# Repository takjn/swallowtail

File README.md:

# Swallowtail
A split keyboard with 5x6 column staggered keys.

## Parts List
### Required

|Name |Number |Notes |
|--- |--- |--- |
|PCB | 2 | This PCB is reversible. One is for left and the other is for right. You can use a gerber file in `pcb/plot` directory to order your one. |
|Top plate, bottom plate, OLED protection plate | 2 sets | You can see the svg file in `plate` directory. This is designed for 2mm acrylic plate. If you create your plate with another thickness or material, you may need to change spacer height and screw length. |
|3mm female-to-female spacer | 12 |https://www.aliexpress.com/item/33033691154.html |
|3mm female-to-male spacer | 16 |https://www.aliexpress.com/item/33033691154.html |
|8mm female-to-female spacer | 4 |https://www.aliexpress.com/item/33033691154.html |
|M2 3mm screw | 32 | 3.5mm will be better if you can get. |
|Diode 1N4148 | 60 | |
|Kailh PCB Socket | 60 | |
|2 pin Tactile switch | 2 | For reset switch |
|3.5mm TRRS jack | 2 | |
|Adhesive Rubber Cushions | 8 | |
|Pro micro | 2 | |
|Cherry MX switch (5 pin) | 60 | |
|Keycaps | 60 | 58 1u keycaps and 2 1.5u (or up to 2.25u) keycaps|
|TRS (3 pole) audio cable | 1 | |
|Micro USB Cable | 1 | |

### Options
#### Spring loaded pin headers
Highly recommend for beginners. Some shop sell it with a Pro micro.
|Name |Number |Notes |
|--- |--- |--- |
|Spring loaded 12-pin header (a.k.a. Conthrough) | 4 |https://talpkeyboard.net/items/5e056626d790db16e2889233  |

#### OLED
Just a decorative parts.
|Name |Number |Notes |
|--- |--- |--- |
|SSD1306 OLED module | 2 | |
|4 pin low profile socket (low profile)| 2 | |
|4 pin low profile header (low profile)| 2 | |

#### Back light
A led places in bottom (south) side of keycap. Transparent key switch is recommended.
|Name |Number |Notes |
|--- |--- |--- |
|SK6812MINI-E | 60 | |

## Build Instructions

### Preparation
#### QMK firmware
Swallowtail uses QMK firmware. See firmware section and flush a firmware to Pro micro in advance.

#### Pro micro
Pro micro USB connector is fragile. You can reinforce the connector with epoxy resin adhesive. Put a small amount of epoxy resin around the connector. Be careful not to flow it into the connector. Leave it until fixed.

### Soldering
All parts have a position and orientation. See the photo to make sure it is placed correctly before soldering.

Maybe a good idea to use masking tape to hold parts before soldering.

#### Bridge jumpers
The PCB is reversible. Use one board for the left and the other for the right.
Bridge five jumpers on each board. One should be "Left" and the other should be "Right".

#### Diode
Place diodes on the back side of the pcb. This is the same side on which you jumpered. Make sure the diode orientation is correct. All diodes orientation must be the same on a pcb.

#### Reset switch and TRRS jack
Solder a reset switch and TRRS jack on the **front** side of the pcb.

#### Pro micro
Insert pin headers from the surface on which parts are mounted. Solder it from the **blank** side of the Pro micro.

Insert a Pro micro into the place on the PCB. If you are using spring loaded pin headers, you don't need to solder it on the PCB so that you can remove Pro micro later easily. If you don't, solder it and cut pins a little not to conflict with the cover plate.

#### Test
Before moving to the next step, test the pcb once. Flash a firmware to the Pro micro. Then, make short-circuit on each keyswitch pads. You will see some characters in your computer.

#### Kailh PCB Socket
Place a PCB socket on the back side of pcb. Make sure the position is correct.

#### OLED (optional)
Place a pin socket on the **front** side and solder it. Then solder a pin header on a OLED.

#### Back light (optional)
See a LED. You will see one of pins' corner is cut. The pin should be placed on the bottom-left in where a "L" shape silk is printed.

LED can be broken easily by heat. Be careful not to take too long time to solder. I usually solder only one pin at once and go to the next LED. After all LEDs in a row is fixed, back to the first LED to solder the second pin and repeat the process. This will be good not to heat too much on a LED.

### Assemble
Screw top plate spacers. 3mm female-to-male spacer should be on the front side. Attach a PCB and fix the PCB with a 3mm female-to-female spacer from the back side.

Screw OLED spacers. Each 8mm female-to-female spacer should be on the front side. Fix the spacer with a 3mm female-to-male spacer from the back side.

Put the bottom plate and OLED protection plate too.

Plug key switches on the top plate. Make sure all pins are straight before insert.

## Firmware
You can use a prebuilt firmware in the firmware directory. Go to [Pro Micro Web Updater](https://sekigon-gonnoc.github.io/promicro-web-updater/index.html) and flash the hex file in the firmware directory.

The firmware supports [Remap](https://remap-keys.app/). You can customize key bindings easily without compile. Go to [Remap](https://remap-keys.app/) and connect your keyboad.

Swallowtail uses QMK firmware. If you want to customize the firmware, see [swallowtail branch in takjn/qmk_firmware](https://github.com/takjn/qmk_firmware/tree/swallowtail/keyboards/swallowtail).

## License
Licensed under the MIT License.

## Dependencies
This PCB uses [foostan/kbd](https://github.com/foostan/kbd) library.

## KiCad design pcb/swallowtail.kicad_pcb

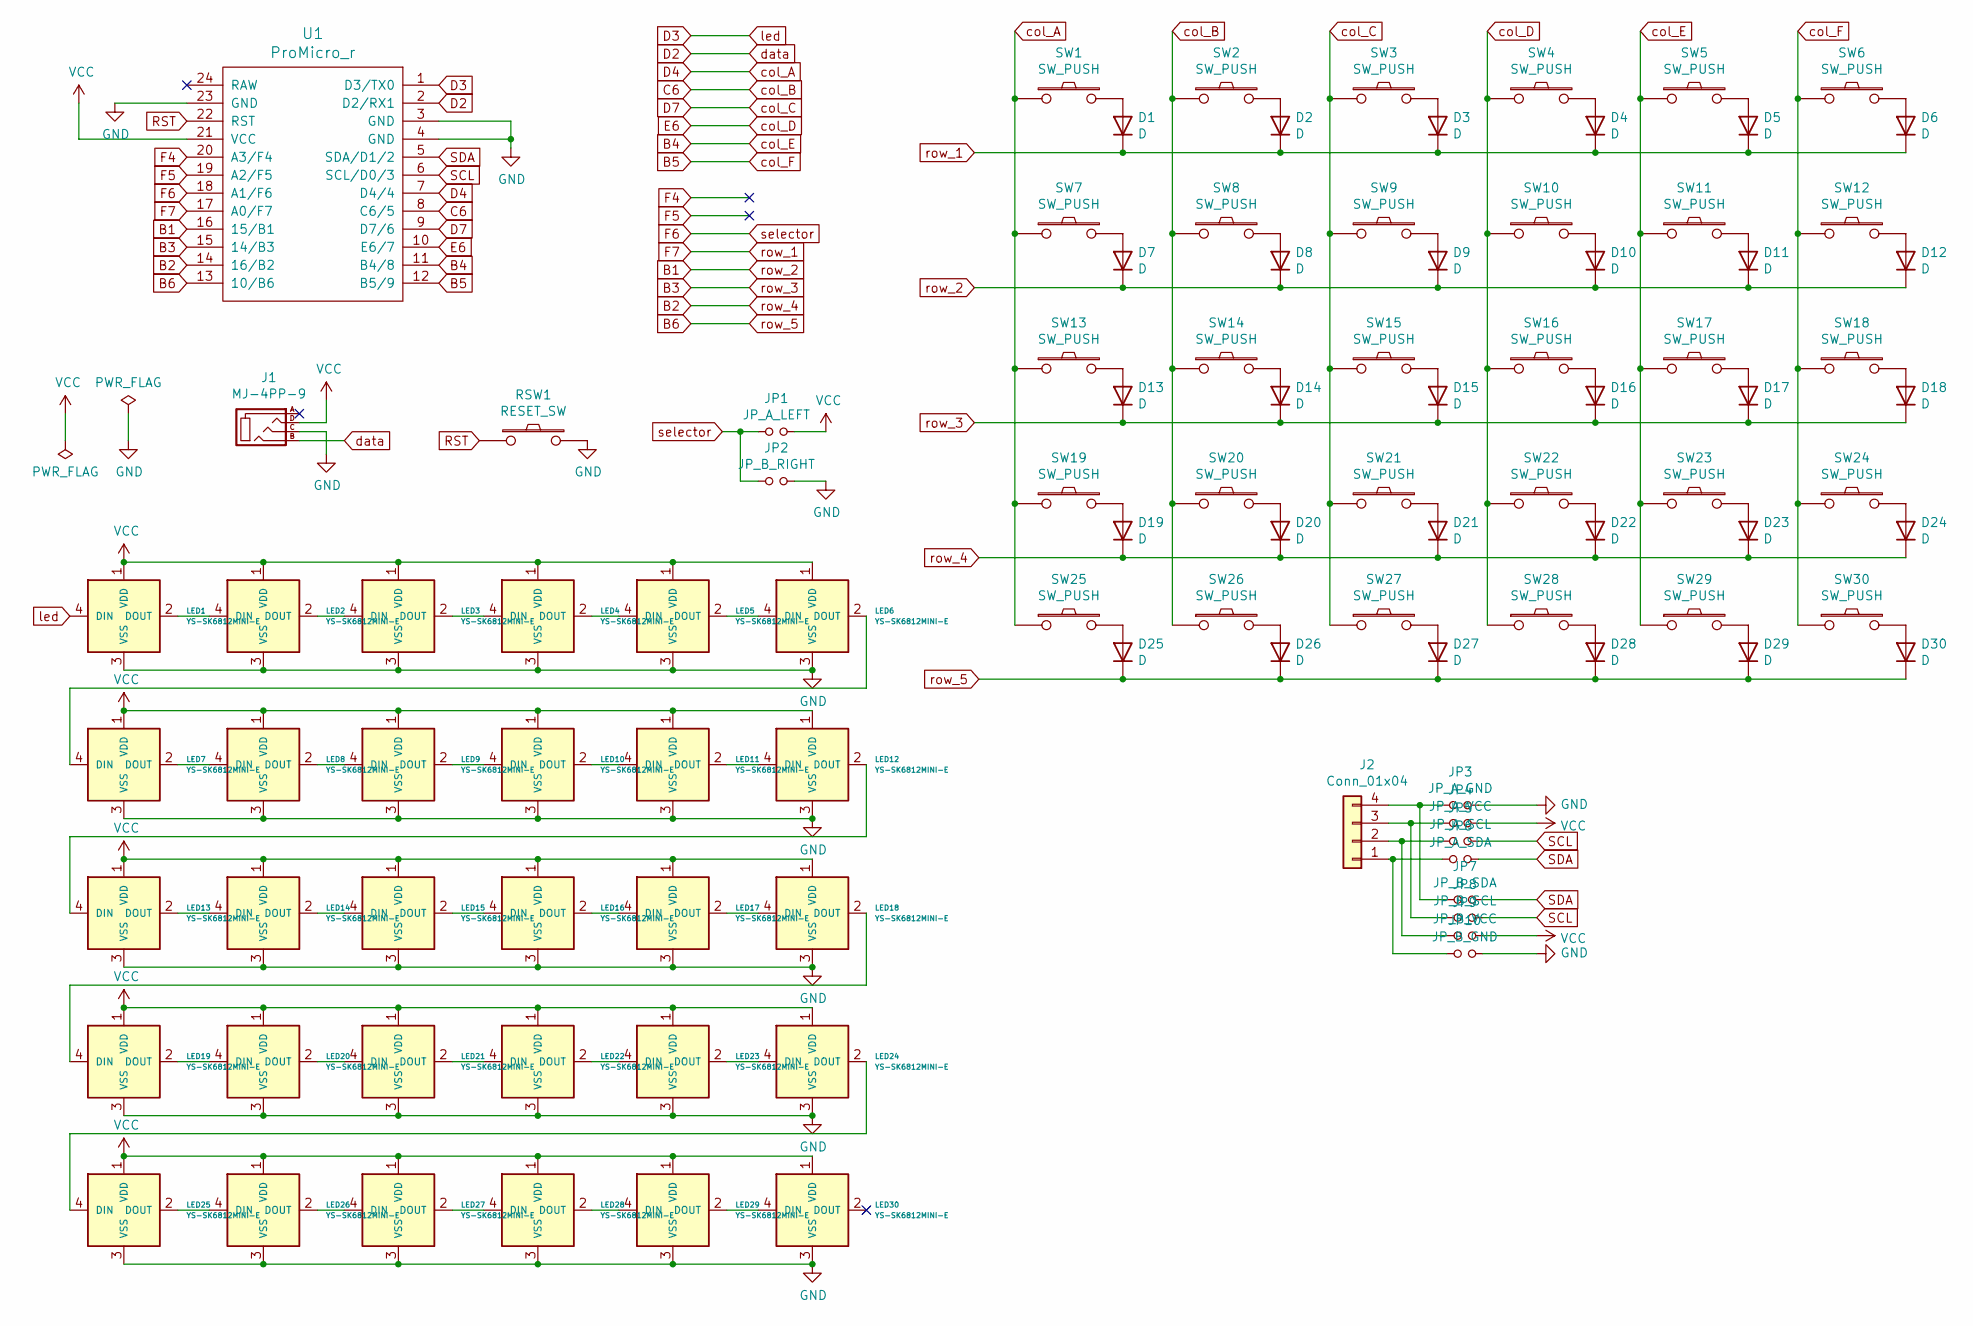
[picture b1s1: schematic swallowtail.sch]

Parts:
D1, D2, D3, D4, D5, D6, D7, D8, D9, D10, D11, D12, D13, D14, D15, D16, D17, D18, D19, D20, D21, D22, D23, D24, D25, D26, D27, D28, D29, D30: D; D3_TH_SMD_v2
J1: MJ-4PP-9
J2: Conn_01x04; OLED
JP1: JP_A_LEFT; Jumper
JP2: JP_B_RIGHT; Jumper
JP3: JP_A_GND; Jumper
JP4: JP_A_VCC; Jumper
JP5: JP_A_SCL; Jumper
JP6: JP_A_SDA; Jumper
JP7: JP_B_SDA; Jumper
JP8: JP_B_SCL; Jumper
JP9: JP_B_VCC; Jumper
JP10: JP_B_GND; Jumper
LED1, LED2, LED3, LED4, LED5, LED6, LED7, LED8, LED9, LED10, LED11, LED12, LED13, LED14, LED15, LED16, LED17, LED18, LED19, LED20, LED21, LED22, LED23, LED24, LED25, LED26, LED27, LED28, LED29, LED30: YS-SK6812MINI-E; YS-SK6812MINI-E_reversible
RSW1: RESET_SW; ResetSW
SW1, SW2, SW3, SW4, SW5, SW6, SW7, SW8, SW9, SW10, SW11, SW12, SW13, SW14, SW15, SW16, SW17, SW18, SW19, SW20, SW21, SW22, SW23, SW24, SW25, SW26, SW27, SW28, SW29: SW_PUSH; CherryMX_MidHeight_Hotswap
SW30: SW_PUSH; CherryMX_MidHeight_Hotswap_1.5u
U1: ProMicro_r; ProMicro_v2_mod

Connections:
B1: D7.1 (K), D8.1 (K), D9.1 (K), D10.1 (K), D11.1 (K), D12.1 (K), U1.16 (15/B1)
B2: D19.1 (K), D20.1 (K), D21.1 (K), D22.1 (K), D23.1 (K), D24.1 (K), U1.14 (16/B2)
B3: D13.1 (K), D14.1 (K), D15.1 (K), D16.1 (K), D17.1 (K), D18.1 (K), U1.15 (14/B3)
B4: SW5.1, SW11.1, SW17.1, SW23.1, SW29.1, U1.11 (B4/8)
B5: SW6.1, SW12.1, SW18.1, SW24.1, SW30.1, U1.12 (B5/9)
B6: D25.1 (K), D26.1 (K), D27.1 (K), D28.1 (K), D29.1 (K), D30.1 (K), U1.13 (10/B6)
C6: SW2.1, SW8.1, SW14.1, SW20.1, SW26.1, U1.8 (C6/5)
D2: J1.B, U1.2 (D2/RX1)
D3: LED1.4 (DIN), U1.1 (D3/TX0)
D4: SW1.1, SW7.1, SW13.1, SW19.1, SW25.1, U1.7 (D4/4)
D7: SW3.1, SW9.1, SW15.1, SW21.1, SW27.1, U1.9 (D7/6)
E6: SW4.1, SW10.1, SW16.1, SW22.1, SW28.1, U1.10 (E6/7)
F4: U1.20 (A3/F4)
F5: U1.19 (A2/F5)
F6: JP1.1, JP2.1, U1.18 (A1/F6)
F7: D1.1 (K), D2.1 (K), D3.1 (K), D4.1 (K), D5.1 (K), D6.1 (K), U1.17 (A0/F7)
GND: J1.C, JP2.2, JP3.2, JP10.2, LED1.3 (VSS), LED2.3 (VSS), LED3.3 (VSS), LED4.3 (VSS), LED5.3 (VSS), LED6.3 (VSS), LED7.3 (VSS), LED8.3 (VSS), LED9.3 (VSS), LED10.3 (VSS), LED11.3 (VSS), LED12.3 (VSS), LED13.3 (VSS), LED14.3 (VSS), LED15.3 (VSS), LED16.3 (VSS), LED17.3 (VSS), LED18.3 (VSS), LED19.3 (VSS), LED20.3 (VSS), LED21.3 (VSS), LED22.3 (VSS), LED23.3 (VSS), LED24.3 (VSS), LED25.3 (VSS), LED26.3 (VSS), LED27.3 (VSS), LED28.3 (VSS), LED29.3 (VSS), LED30.3 (VSS), RSW1.2, U1.3 (GND), U1.4 (GND), U1.23 (GND)
unnamed: D1.2 (A), SW1.2
unnamed: D2.2 (A), SW2.2
unnamed: D3.2 (A), SW3.2
unnamed: D4.2 (A), SW4.2
unnamed: D5.2 (A), SW5.2
unnamed: D6.2 (A), SW6.2
unnamed: D7.2 (A), SW7.2
unnamed: D8.2 (A), SW8.2
unnamed: D9.2 (A), SW9.2
unnamed: D10.2 (A), SW10.2
unnamed: D11.2 (A), SW11.2
unnamed: D12.2 (A), SW12.2
unnamed: D13.2 (A), SW13.2
unnamed: D14.2 (A), SW14.2
unnamed: D15.2 (A), SW15.2
unnamed: D16.2 (A), SW16.2
unnamed: D17.2 (A), SW17.2
unnamed: D18.2 (A), SW18.2
unnamed: D19.2 (A), SW19.2
unnamed: D20.2 (A), SW20.2
unnamed: D21.2 (A), SW21.2
unnamed: D22.2 (A), SW22.2
unnamed: D23.2 (A), SW23.2
unnamed: D24.2 (A), SW24.2
unnamed: D25.2 (A), SW25.2
unnamed: D26.2 (A), SW26.2
unnamed: D27.2 (A), SW27.2
unnamed: D28.2 (A), SW28.2
unnamed: D29.2 (A), SW29.2
unnamed: D30.2 (A), SW30.2
unnamed: J2.1, JP6.1, JP10.1
unnamed: J2.2, JP5.1, JP9.1
unnamed: J2.3, JP4.1, JP8.1
unnamed: J2.4, JP3.1, JP7.1
unnamed: LED1.2 (DOUT), LED2.4 (DIN)
unnamed: LED2.2 (DOUT), LED3.4 (DIN)
unnamed: LED3.2 (DOUT), LED4.4 (DIN)
unnamed: LED4.2 (DOUT), LED5.4 (DIN)
unnamed: LED5.2 (DOUT), LED6.4 (DIN)
unnamed: LED6.2 (DOUT), LED7.4 (DIN)
unnamed: LED7.2 (DOUT), LED8.4 (DIN)
unnamed: LED8.2 (DOUT), LED9.4 (DIN)
unnamed: LED10.2 (DOUT), LED11.4 (DIN)
unnamed: LED9.2 (DOUT), LED10.4 (DIN)
unnamed: LED11.2 (DOUT), LED12.4 (DIN)
unnamed: LED12.2 (DOUT), LED13.4 (DIN)
unnamed: LED13.2 (DOUT), LED14.4 (DIN)
unnamed: LED14.2 (DOUT), LED15.4 (DIN)
unnamed: LED15.2 (DOUT), LED16.4 (DIN)
unnamed: LED16.2 (DOUT), LED17.4 (DIN)
unnamed: LED17.2 (DOUT), LED18.4 (DIN)
unnamed: LED18.2 (DOUT), LED19.4 (DIN)
unnamed: LED19.2 (DOUT), LED20.4 (DIN)
unnamed: LED20.2 (DOUT), LED21.4 (DIN)
unnamed: LED21.2 (DOUT), LED22.4 (DIN)
unnamed: LED22.2 (DOUT), LED23.4 (DIN)
unnamed: LED23.2 (DOUT), LED24.4 (DIN)
unnamed: LED24.2 (DOUT), LED25.4 (DIN)
unnamed: LED25.2 (DOUT), LED26.4 (DIN)
unnamed: LED26.2 (DOUT), LED27.4 (DIN)
unnamed: LED27.2 (DOUT), LED28.4 (DIN)
unnamed: LED28.2 (DOUT), LED29.4 (DIN)
unnamed: LED29.2 (DOUT), LED30.4 (DIN)
RST: RSW1.1, U1.22 (RST)
SCL: JP5.2, JP8.2, U1.6 (SCL/D0/3)
SDA: JP6.2, JP7.2, U1.5 (SDA/D1/2)
VCC: J1.D, JP1.2, JP4.2, JP9.2, LED1.1 (VDD), LED2.1 (VDD), LED3.1 (VDD), LED4.1 (VDD), LED5.1 (VDD), LED6.1 (VDD), LED7.1 (VDD), LED8.1 (VDD), LED9.1 (VDD), LED10.1 (VDD), LED11.1 (VDD), LED12.1 (VDD), LED13.1 (VDD), LED14.1 (VDD), LED15.1 (VDD), LED16.1 (VDD), LED17.1 (VDD), LED18.1 (VDD), LED19.1 (VDD), LED20.1 (VDD), LED21.1 (VDD), LED22.1 (VDD), LED23.1 (VDD), LED24.1 (VDD), LED25.1 (VDD), LED26.1 (VDD), LED27.1 (VDD), LED28.1 (VDD), LED29.1 (VDD), LED30.1 (VDD), U1.21 (VCC)

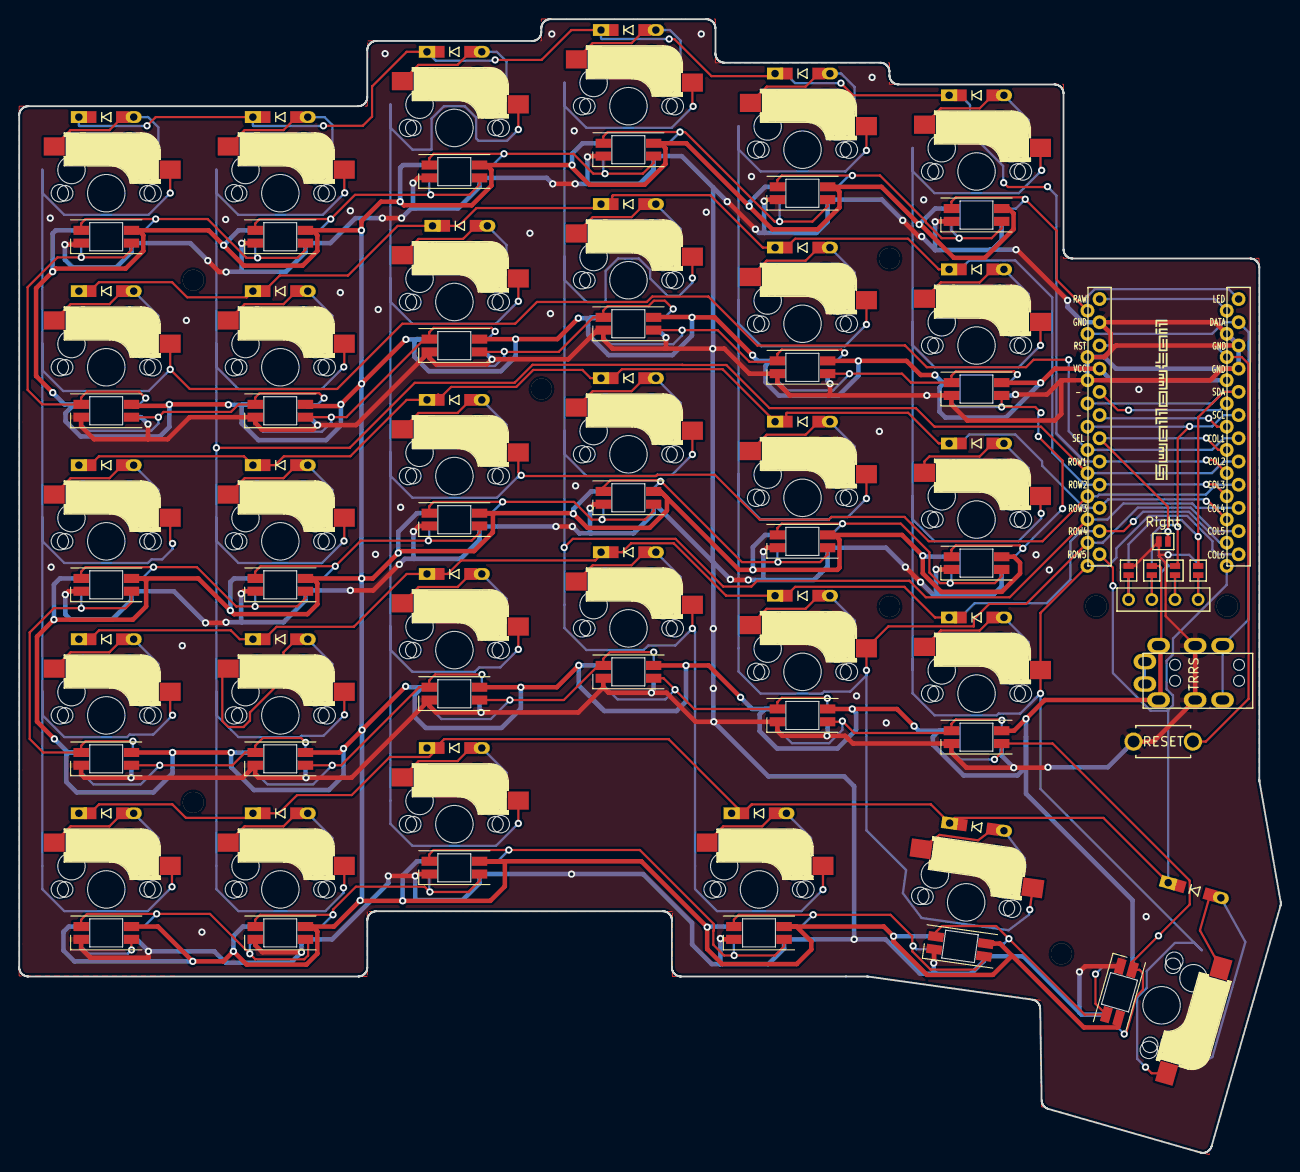
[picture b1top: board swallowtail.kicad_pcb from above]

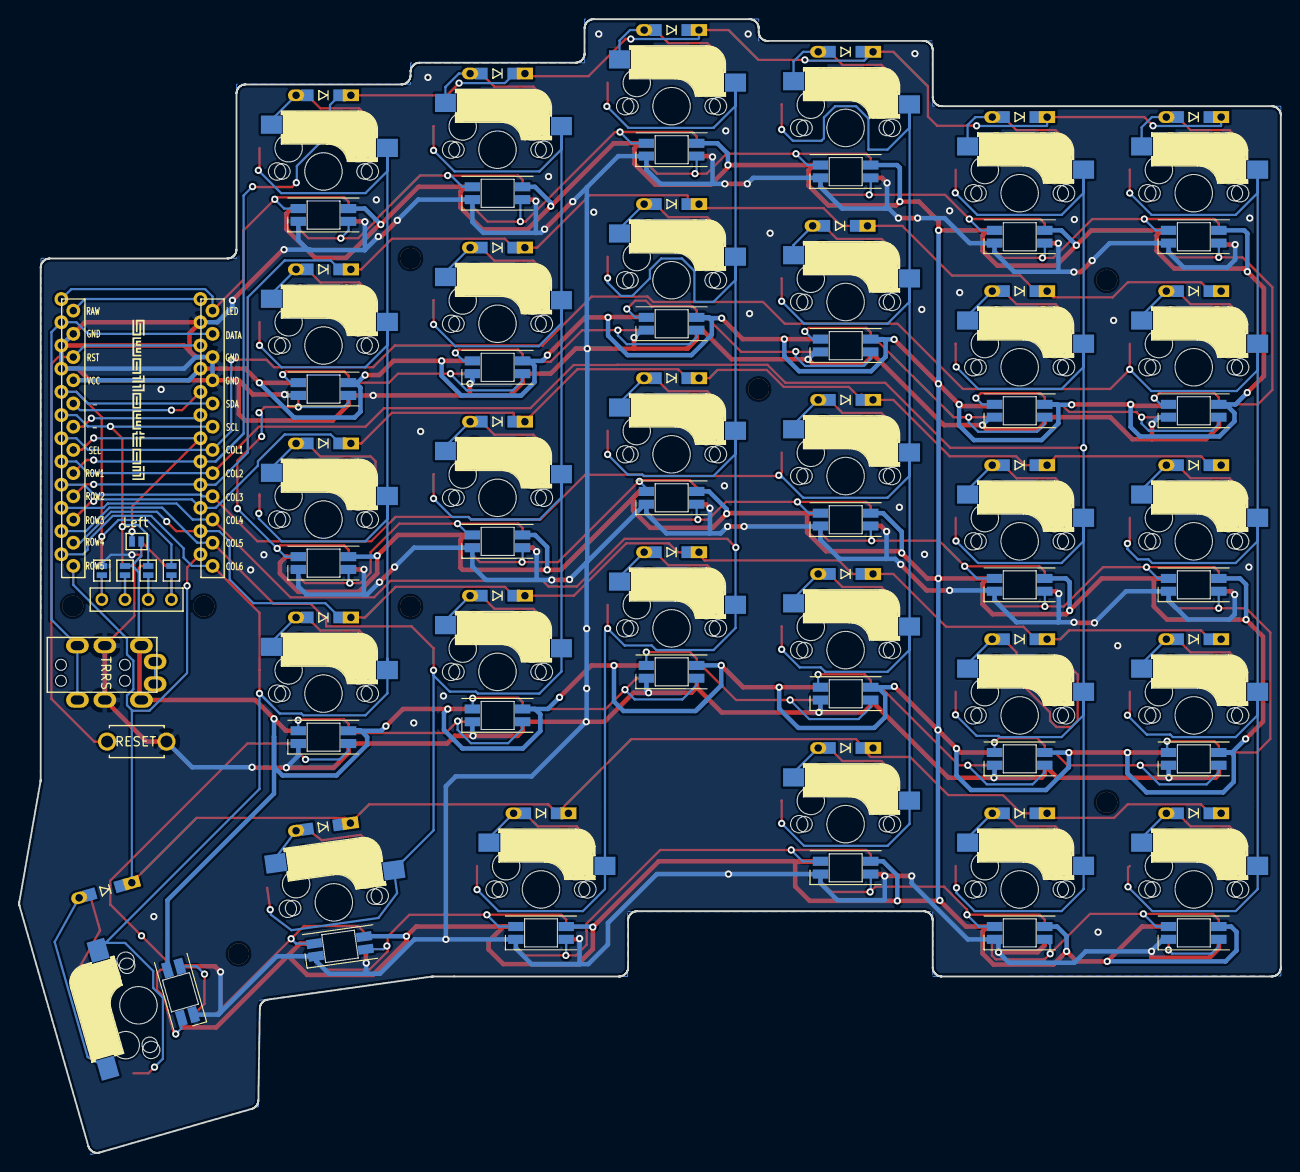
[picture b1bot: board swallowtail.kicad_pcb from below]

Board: 2 copper layers, 138.1 x 124.1 mm, 112 parts (5 on the bottom side), 82 nets.

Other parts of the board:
Ref**: Val**; M2_Threads_v2
Ref**#2, Ref**#3, Ref**#4, Ref**#5, Ref**#6, Ref**#7, Ref**#8: Val**; M2_Threads_v2

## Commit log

2021-04-01 init
2021-04-01 add misc
2021-04-18 add README
2021-04-20 add schema pdf
2021-04-20 add foostan/kbd as a submodule
2021-08-08 v2 design
2021-10-15 add precompiled firmware
2021-10-16 add RGB matrix firmware
2021-10-16 fix json file
